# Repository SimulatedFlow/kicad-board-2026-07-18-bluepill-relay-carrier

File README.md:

# 2026-07-18-bluepill-relay-carrier

<!-- SF-STORE-BLOCK:BEGIN -->
## 🛒 Source-available — see before you buy

This repository contains the **full design files** of a commercial hardware board. It is **source-available, not open source**: read it, evaluate it, then buy a license to use it. See **LICENSE.md (source-available, purchase required)**.

**Get it / Buy:**
- eBay store — all our boards and PCB art: https://www.ebay.de/usr/simula-9
- Merch shop (dev & gaming): https://simulatedflow.myspreadshop.de
- Merch shop (Synthetica / EDM): https://synthetica.myspreadshop.de
- Direct / invoice (Simulated Flow UG): simulatedflow@gmail.com

_This board has no eBay item number of its own listed here — the store link above holds all current listings._

### 📬 **Free Board Documentation & Firmware Pack**

Schematics, BOMs and example-firmware docs for our STM32 carrier boards. Get it by joining the newsletter — plus a heads-up when something new ships. Double opt-in, unsubscribe in one click, no address sharing.

👉 **[Get the free pack](https://simulatedflow.teufel-engineering.com/newsletter/hardware/?q=gh)**

_© 2026 Simulated Flow UG. All rights reserved._
<!-- SF-STORE-BLOCK:END -->

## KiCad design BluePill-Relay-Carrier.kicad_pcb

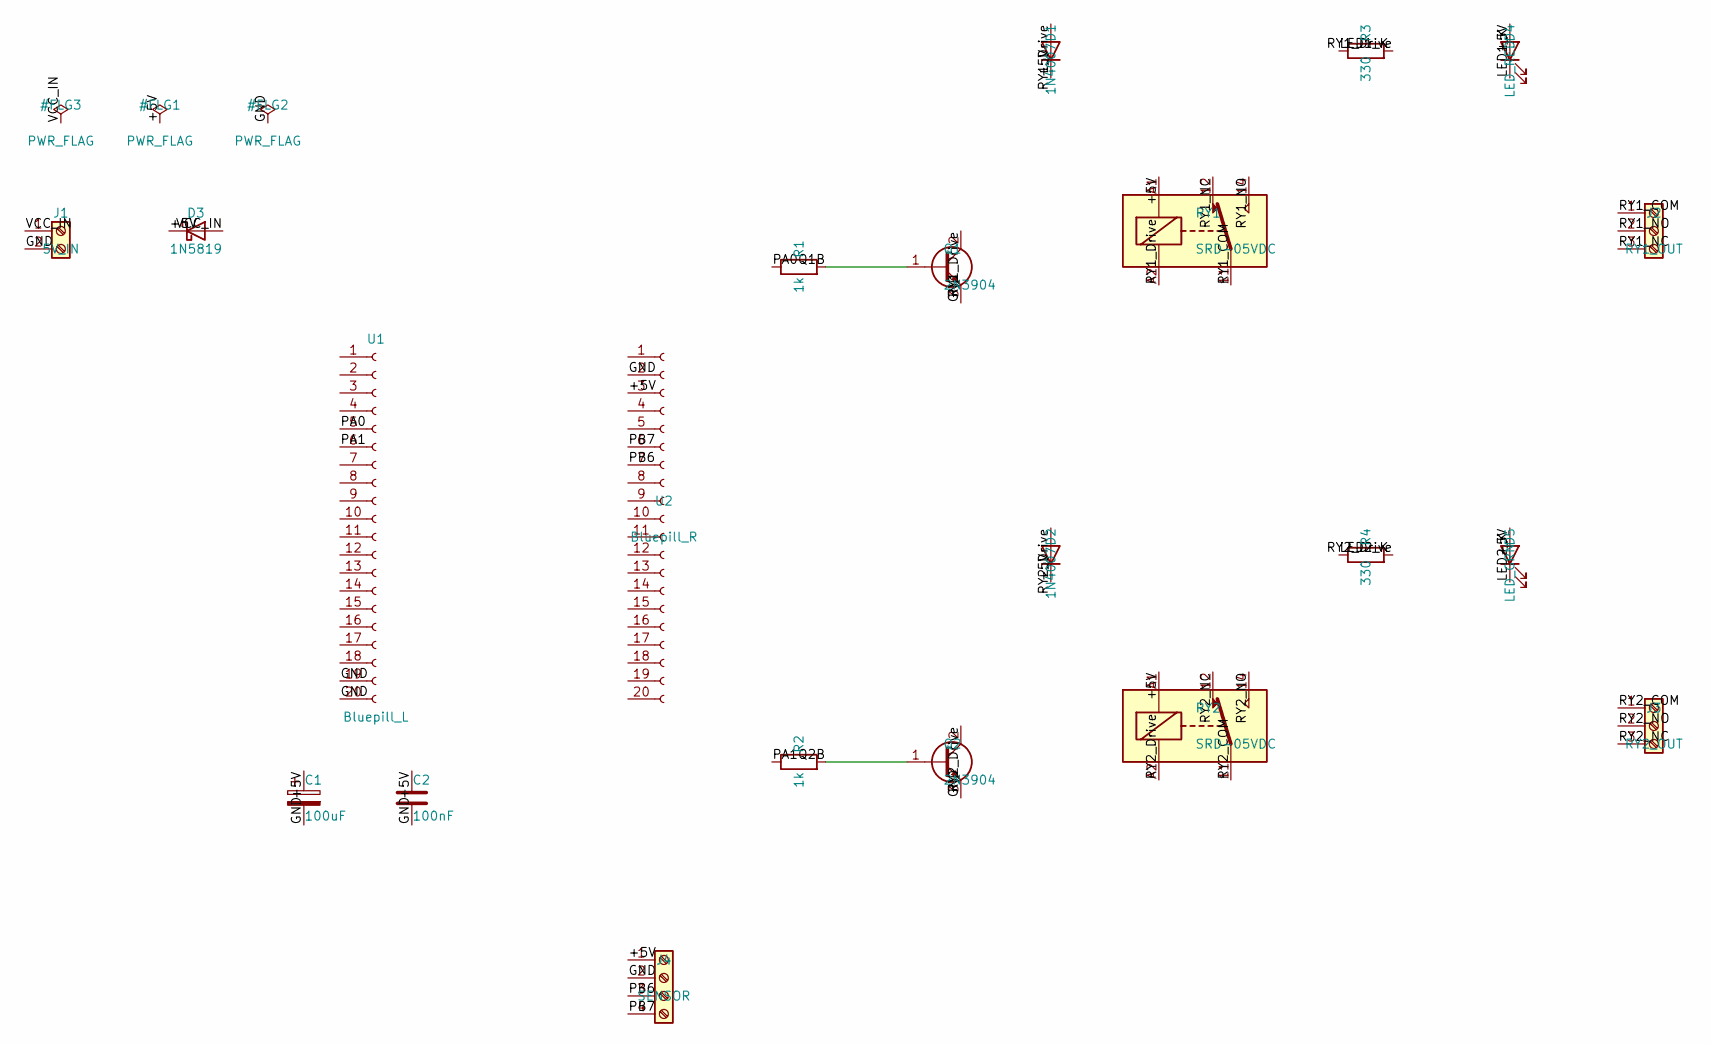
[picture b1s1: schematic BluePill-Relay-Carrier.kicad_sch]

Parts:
C1: 100uF; CP_Radial_D6.3mm_P2.50mm
C2: 100nF; C_Disc_D5.0mm_W2.5mm_P5.00mm
D1, D2: 1N4007; D_DO-41_SOD81_P10.16mm_Horizontal
D3: 1N5819; D_DO-41_SOD81_P10.16mm_Horizontal
D4: LED_RED; LED_D3.0mm
D5: LED_GRN; LED_D3.0mm
J1: 5V_IN; TerminalBlock_Phoenix_PT-1,5-2-5.0-H_1x02_P5.00mm_Horizontal
J2: RY1_OUT; TerminalBlock_Phoenix_PT-1,5-3-5.0-H_1x03_P5.00mm_Horizontal
J3: RY2_OUT; TerminalBlock_Phoenix_PT-1,5-3-5.0-H_1x03_P5.00mm_Horizontal
J4: SENSOR; TerminalBlock_Phoenix_PT-1,5-4-5.0-H_1x04_P5.00mm_Horizontal
Q1, Q2: 2N3904; TO-92_Inline
R1, R2: 1k; R_Axial_DIN0207_L6.3mm_D2.5mm_P10.16mm_Horizontal
R3, R4: 330; R_Axial_DIN0207_L6.3mm_D2.5mm_P10.16mm_Horizontal
RY1, RY2: SRD-05VDC; Relay_SPDT_Hongfa_JQC-3FF_0XX-1Z
U1: Bluepill_L; PinSocket_1x20_P2.54mm_Vertical
U2: Bluepill_R; PinSocket_1x20_P2.54mm_Vertical

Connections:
+5V: C1.1, C2.1, D1.1 (K), D2.1 (K), D3.1 (K), D4.2 (A), D5.2 (A), J4.1, RY1.A1, RY2.A1, U2.3
GND: C1.2, C2.2, J1.2, J4.2, Q1.3 (E), Q2.3 (E), U1.19, U1.20, U2.2
LED1_K: D4.1 (K), R3.1
LED2_K: D5.1 (K), R4.1
PA0: R1.1, U1.5
PA1: R2.1, U1.6
PB6: J4.3, U2.7
PB7: J4.4, U2.6
Q1B: Q1.1 (B), R1.2
Q2B: Q2.1 (B), R2.2
RY1_COM: J2.1, RY1.11
RY1_Drive: D1.2 (A), Q1.2 (C), R3.2, RY1.A2
RY1_NC: J2.3, RY1.12
RY1_NO: J2.2, RY1.14
RY2_COM: J3.1, RY2.11
RY2_Drive: D2.2 (A), Q2.2 (C), R4.2, RY2.A2
RY2_NC: J3.3, RY2.12
RY2_NO: J3.2, RY2.14
VCC_IN: D3.2 (A), J1.1

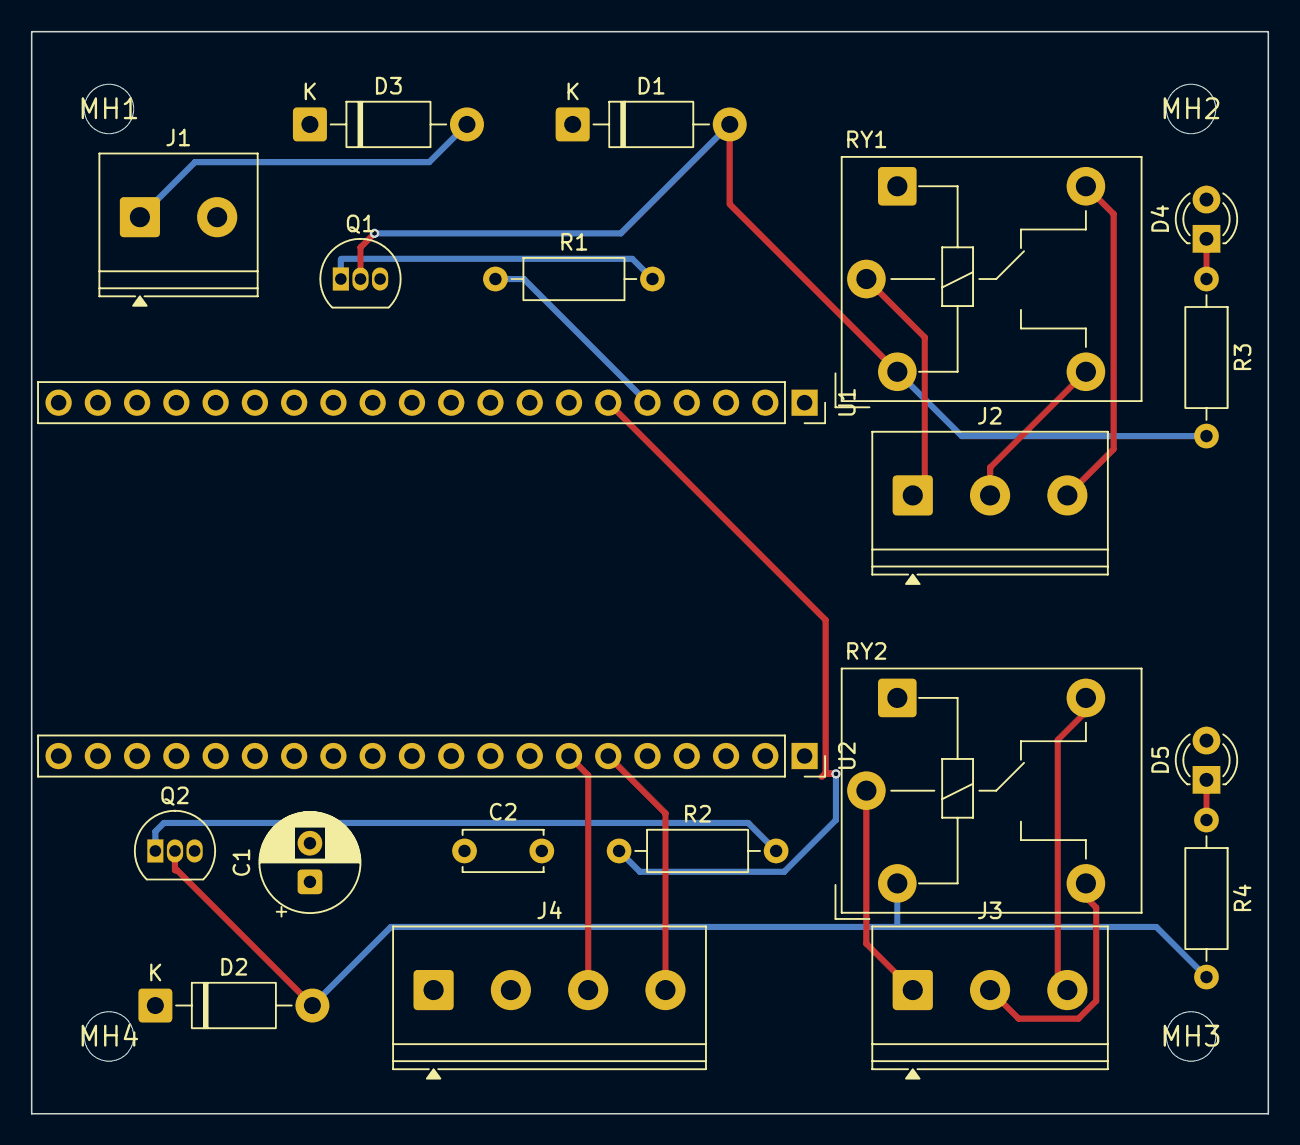
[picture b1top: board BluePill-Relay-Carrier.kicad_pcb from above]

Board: 4 copper layers, 80.0 x 70.0 mm, 25 parts (0 on the bottom side), 19 nets.

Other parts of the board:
MH1, MH2, MH3, MH4: MountingHole_3.2mm

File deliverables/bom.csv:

"Refs","Value","Footprint","Qty","DNP"
"C1","100uF","Capacitor_THT:CP_Radial_D6.3mm_P2.50mm","1",""
"C2","100nF","Capacitor_THT:C_Disc_D5.0mm_W2.5mm_P5.00mm","1",""
"D1","1N4007","Diode_THT:D_DO-41_SOD81_P10.16mm_Horizontal","1",""
"D2","1N4007","Diode_THT:D_DO-41_SOD81_P10.16mm_Horizontal","1",""
"D3","1N5819","Diode_THT:D_DO-41_SOD81_P10.16mm_Horizontal","1",""
"D4","LED_RED","LED_THT:LED_D3.0mm","1",""
"D5","LED_GRN","LED_THT:LED_D3.0mm","1",""
"J1","5V_IN","TerminalBlock_Phoenix:TerminalBlock_Phoenix_PT-1,5-2-5.0-H_1x02_P5.00mm_Horizontal","1",""
"J2","RY1_OUT","TerminalBlock_Phoenix:TerminalBlock_Phoenix_PT-1,5-3-5.0-H_1x03_P5.00mm_Horizontal","1",""
"J3","RY2_OUT","TerminalBlock_Phoenix:TerminalBlock_Phoenix_PT-1,5-3-5.0-H_1x03_P5.00mm_Horizontal","1",""
"J4","SENSOR","TerminalBlock_Phoenix:TerminalBlock_Phoenix_PT-1,5-4-5.0-H_1x04_P5.00mm_Horizontal","1",""
"Q1","2N3904","Package_TO_SOT_THT:TO-92_Inline","1",""
"Q2","2N3904","Package_TO_SOT_THT:TO-92_Inline","1",""
"R1","1k","Resistor_THT:R_Axial_DIN0207_L6.3mm_D2.5mm_P10.16mm_Horizontal","1",""
"R2","1k","Resistor_THT:R_Axial_DIN0207_L6.3mm_D2.5mm_P10.16mm_Horizontal","1",""
"R3","330","Resistor_THT:R_Axial_DIN0207_L6.3mm_D2.5mm_P10.16mm_Horizontal","1",""
"R4","330","Resistor_THT:R_Axial_DIN0207_L6.3mm_D2.5mm_P10.16mm_Horizontal","1",""
"RY1","SRD-05VDC","Relay_THT:Relay_SPDT_Hongfa_JQC-3FF_0XX-1Z","1",""
"RY2","SRD-05VDC","Relay_THT:Relay_SPDT_Hongfa_JQC-3FF_0XX-1Z","1",""
"U1","Bluepill_L","Connector_PinSocket_2.54mm:PinSocket_1x20_P2.54mm_Vertical","1",""
"U2","Bluepill_R","Connector_PinSocket_2.54mm:PinSocket_1x20_P2.54mm_Vertical","1",""
